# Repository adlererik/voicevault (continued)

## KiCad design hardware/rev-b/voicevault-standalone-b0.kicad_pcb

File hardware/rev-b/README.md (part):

# VoiceVault standalone prototype B0

**Routing in progress — not a working or fabrication-ready PCB.**

[Clean Quilter placement and routing (14 November)](../evidence/2026-11-14/quilter-clean-start/README.md) is now running with the same selected circuit/parts, zero previous tracks/vias/pours, and 292 components for Quilter to place. Its own fanout and routing are enabled; only 22 mechanical/access/antenna anchors remain fixed. All prior work is backed up. The earlier 89%-routed result failed native review; the next corrected trial failed without routed candidates after 29h 27m. Neither replaced the live PCB. [Full history and limits](QUILTER_ROUTING.md).

VoiceVault moves plaintext voice, keys, contacts and call approval into a dedicated device. An already compromised phone carries encrypted records over BLE. This custom rectangular SMD board uses the identified **Trezor Safe 7 TS7 rev_D core ICs**, with added wired headset audio, physical microphone disconnect, offline microSD and separate computer-debug connections. It replaces the earlier development-board carrier as the active hardware design.

The current native KiCad project contains **296 electrical components, 14 board-only probe pads and four mounting holes** on a provisional **70 × 45 mm**, six-layer, 1.0 mm board. Components are placed on both sides. The latest complete-board autorouter checkpoint **fails native DRC: 280 connections remain unrouted, with 33 layout errors and 100 warnings**; exact sourcing and HDI stackup are unresolved, and no physical board has been tested. [Machine-readable status](STATUS.json) · [Recorded evidence and images](../evidence/2026-11-12/README.md)

*Native KiCad exports, front and rear. RF copper and ground pours are present; most signal and power routing remains incomplete.*

## Open and inspect

From the repository root, run `./hardware/open`. The launcher opens one PCB editor and reuses it to limit memory use. Open `voicevault-standalone-b0.kicad_pro` in KiCad to inspect the root schematic and its **18 child sheets**. Keep the large schematic/3D viewers closed when running routing studies on this computer.

KiCad 10.0.8 uses the local `voicevault-kicad` MCP connection through its official IPC API. Circuit simulation uses **ngspice 47 directly**, preserving actual netlists, logs and measurements. MCP is useful for editor interaction; it is not required to run a command-line simulator. [Tool setup](../README.md)

```sh
./hardware/check --design-only --spice
```

This runs native schematic/pad/net checks, ST ball/function comparisons, ERC/DRC, an antenna-rule negative control, **799 ngspice model cases**, and the explicit power-allocation study. Exit 0 with `--design-only` means the available checks passed. The report still says **manufacturing blocked**. Without that option, exit 2 preserves the blocked release verdict. Exit 1 means a check failed. The historical carrier checks remain available as `./hardware/check --rev-a --design-only`.

## Circuit architecture

| Area | Current circuit intent |
|---|---|
| Trusted compute | STM32U5G9ZJJ6Q, UFBGA144, with local clocks, reset, decoupling and internal-SMPS network. The local symbol restores two power balls missing in the installed library. All 144 ball names and 29 selected peripheral functions are compared with separately pinned ST data. |
| Power and battery | nPM1300 dual 200 mA bucks/charger; USB power-only entry, diode-isolated Qi entry, protected battery connector and external cell-temperature input. USB has no D+/D− contacts. Charging configuration and thermal qualification remain open. |
| Secure elements | TROPIC01 and OPTIGA Trust M on MCU-only buses with local power gates. These circuits do not demonstrate lifecycle configuration, entropy quality or secret protection on real silicon. |
| Hostile radio boundary | nRF52832-CIAA with separate SWD and radio power, fixed-direction SN74AXC4T774 bridges, reset control and default-disabled interface. UART carries bounded records; the radio has no audio, secure-element or MCU-debug wires. Electrical fault containment still needs bench tests. |
| Voice | TLV320AIC3204, SAI1 full duplex, dedicated switched audio regulator, CTIA 3.5 mm headset jack, headphone DC-blocking networks, ESD parts and a physical microphone disconnect. All codec controls stay on the trusted MCU side. |
| Trusted interface | Newhaven 240 × 320 display/touch candidate, local reset/update buttons and DRV2624 haptic driver. These require new VoiceVault drivers; this is not the Safe 7 private display assembly. |
| Offline updates | Locally powered microSD SPI interface with default-disabled signal bridge. Signed-image, rollback and interrupted-update policies exist in the software model; they have not been ported and qualified as this board's boot/update firmware. |
| Qi | STWLC38 receiver, coil resonance/rectifier components, thermal sensing and disable path. Its host-control bus is separate from PMIC and secure-element buses. Matching, configuration, charging and temperature behavior are unqualified. |
| NFC | ST25R3916B with dedicated regulator, bridges and matching network; default-off intent. Firmware must require an explicit local enrollment action. An NFC transport is not itself proof of contact identity. |
| Bench access | Main STDC14 and independent Nordic SWD headers, 14 probe pads and removable audio-current link. Prototype debug access deliberately exposes memory/firmware to trusted lab equipment. |

Read [circuit and power review](CIRCUIT_REVIEW.md), [computer connection and bring-up](DEBUG_AND_BRINGUP.md), and [display/battery adaptations](DISPLAY_BATTERY_CANDIDATES.md) before hardware work.

## Exact reference and differences

The source is pinned to trezor/trezor-hardware commit `d99ad42320a19875c124445195fa56f0dbaff6db`. The actual Safe 7 MCU is **STM32U5G9ZJJ6Q in UFBGA144**, not the LQFP144 STM32U5G9ZJT6Q on the DK2 reference board. The earlier DK2 pin allocations and hardware measurements cannot be assumed to apply to this PCB. Actual silicon revision is not yet verified.

The ten core selections are STM32U5G9ZJJ6Q, nPM1300-CAAA, TPS3420DDRYR, STWLC38JRM, nRF52832-CIAA, ST25R3916B-BWLT, SLS32AIA010MKUSON10XTMA2, TPS61062YZFR, DRV2624YFFR and the TROPIC01 family. TPS61062's `R` suffix selects tape/reel packaging. **TROPIC01's orderable silicon/provisioning revision remains unresolved. OPTIGA's reference order code is NRND.** [Core source table](core-parts.csv)

The published Safe 7 release contains PDFs and board views; it does not supply a complete editable manufacturing project or its private display/battery assemblies. This is a new VoiceVault layout, with catalogue display/battery candidates and added audio/card/debug circuitry. AO3401A power-gate FETs are an explicit adaptation from the reference CSD25501F3. New crystals, antenna/coil geometry, power loads and enclosure need their own validation. No Trezor factory identities, attestation keys or certification are reproduced.

## What the evidence establishes

The native export and actual PCB pads agree for 1,026 schematic-connected nodes and 124 intentional NC pins. The schematic's 323 exported net records include those virtual NC records; the PCB has **199 named copper nets**. The saved pre-autoroute check had zero ERC issues and zero layout violations. After the complete-board SES import and copper refill, native KiCad reports **280 open connections, 33 layout errors and 100 warnings**. The detailed list and independent full ratsnest both report 280. [Final native result](../evidence/2026-11-12/autoroute/README.md).

The antenna restriction is tested on a copy: headless KiCad rejects an unrelated track and a ground via inside the reserved area, and permits the RF-feed track. The live design is checked to remain unchanged. This verifies a CAD rule, not antenna performance or isolation from a physical attacker.

The 799 SPICE cases cover 27 passive MCU-supply sensitivities, 36 headphone cases, 32 microphone/contact cases and 704 static backlight load/fault cases. **They use explicit ideal sources and assumed impedances; no MCU, codec, converter control-loop, battery, RF or charging silicon model is supplied.** [Models, measurements and limits](SPICE_RESULTS.md)

The historical live checkpoint uses official, unmodified **FreeRouting 2.5.0**, headlessly on OpenJDK 25.0.4.1. Its 30-minute job deadline produced an SES containing 1,863 track segments and 274 vias (53 laser). The complete copper result was imported through kipy into the live KiCad editor, preserving all 314 component placements and the original zones, then the zones were refilled. **This is an unfinished routing checkpoint:** native DRC found two antenna-area violations, twelve undersized tracks, nineteen starved thermals and one hundred dangling-copper warnings, plus 280 open connections. [Run, files and actual native DRC](../evidence/2026-11-12/autoroute/README.md).

The prior 448-item checkpoint and older timed-out, unapplied studies are retained as historical evidence. [Routing workflow, bridge and process assumptions](ROUTING.md). Power widths, return paths, clock/analog routing, fine-pitch assembly and the factory stackup still need review; no constraints were relaxed to make this result pass.

[Manufacturing-cost research](MANUFACTURING_COST.md) covers four assemblies delivered to Sweden. The routing target is a provisional six-layer first-order HDI construction, with purchasing left open. No supplier is proven cheapest by a complete delivered quotation.

## Manufacturing release is blocked

[circuit-inventory.csv](circuit-inventory.csv) lists every native electrical component and its current requirements. It is **not a JLCPCB assembly BOM**: generic passives, some connector/assembly variants, lifecycle issues and procurement acceptance are still unresolved. The source inventory of 243 upstream component-unit records is historical reference data, not this board's BOM.

The [13 November parts shortlist](PARTS_SELECTION.md) adds catalogue candidates for 182 components in 29 order-code groups, with primary sources, nominal-rating checks and quantities for four fitted boards. Another 56 components still lack a candidate. Tolerance mismatches are explicitly rejected/held. The separate C502 battery-decoupling correction passed native checks on an isolated copy; it is not in the live board, but is included in the clean cloud input. Neither the shortlist nor the correction is an assembly release.

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
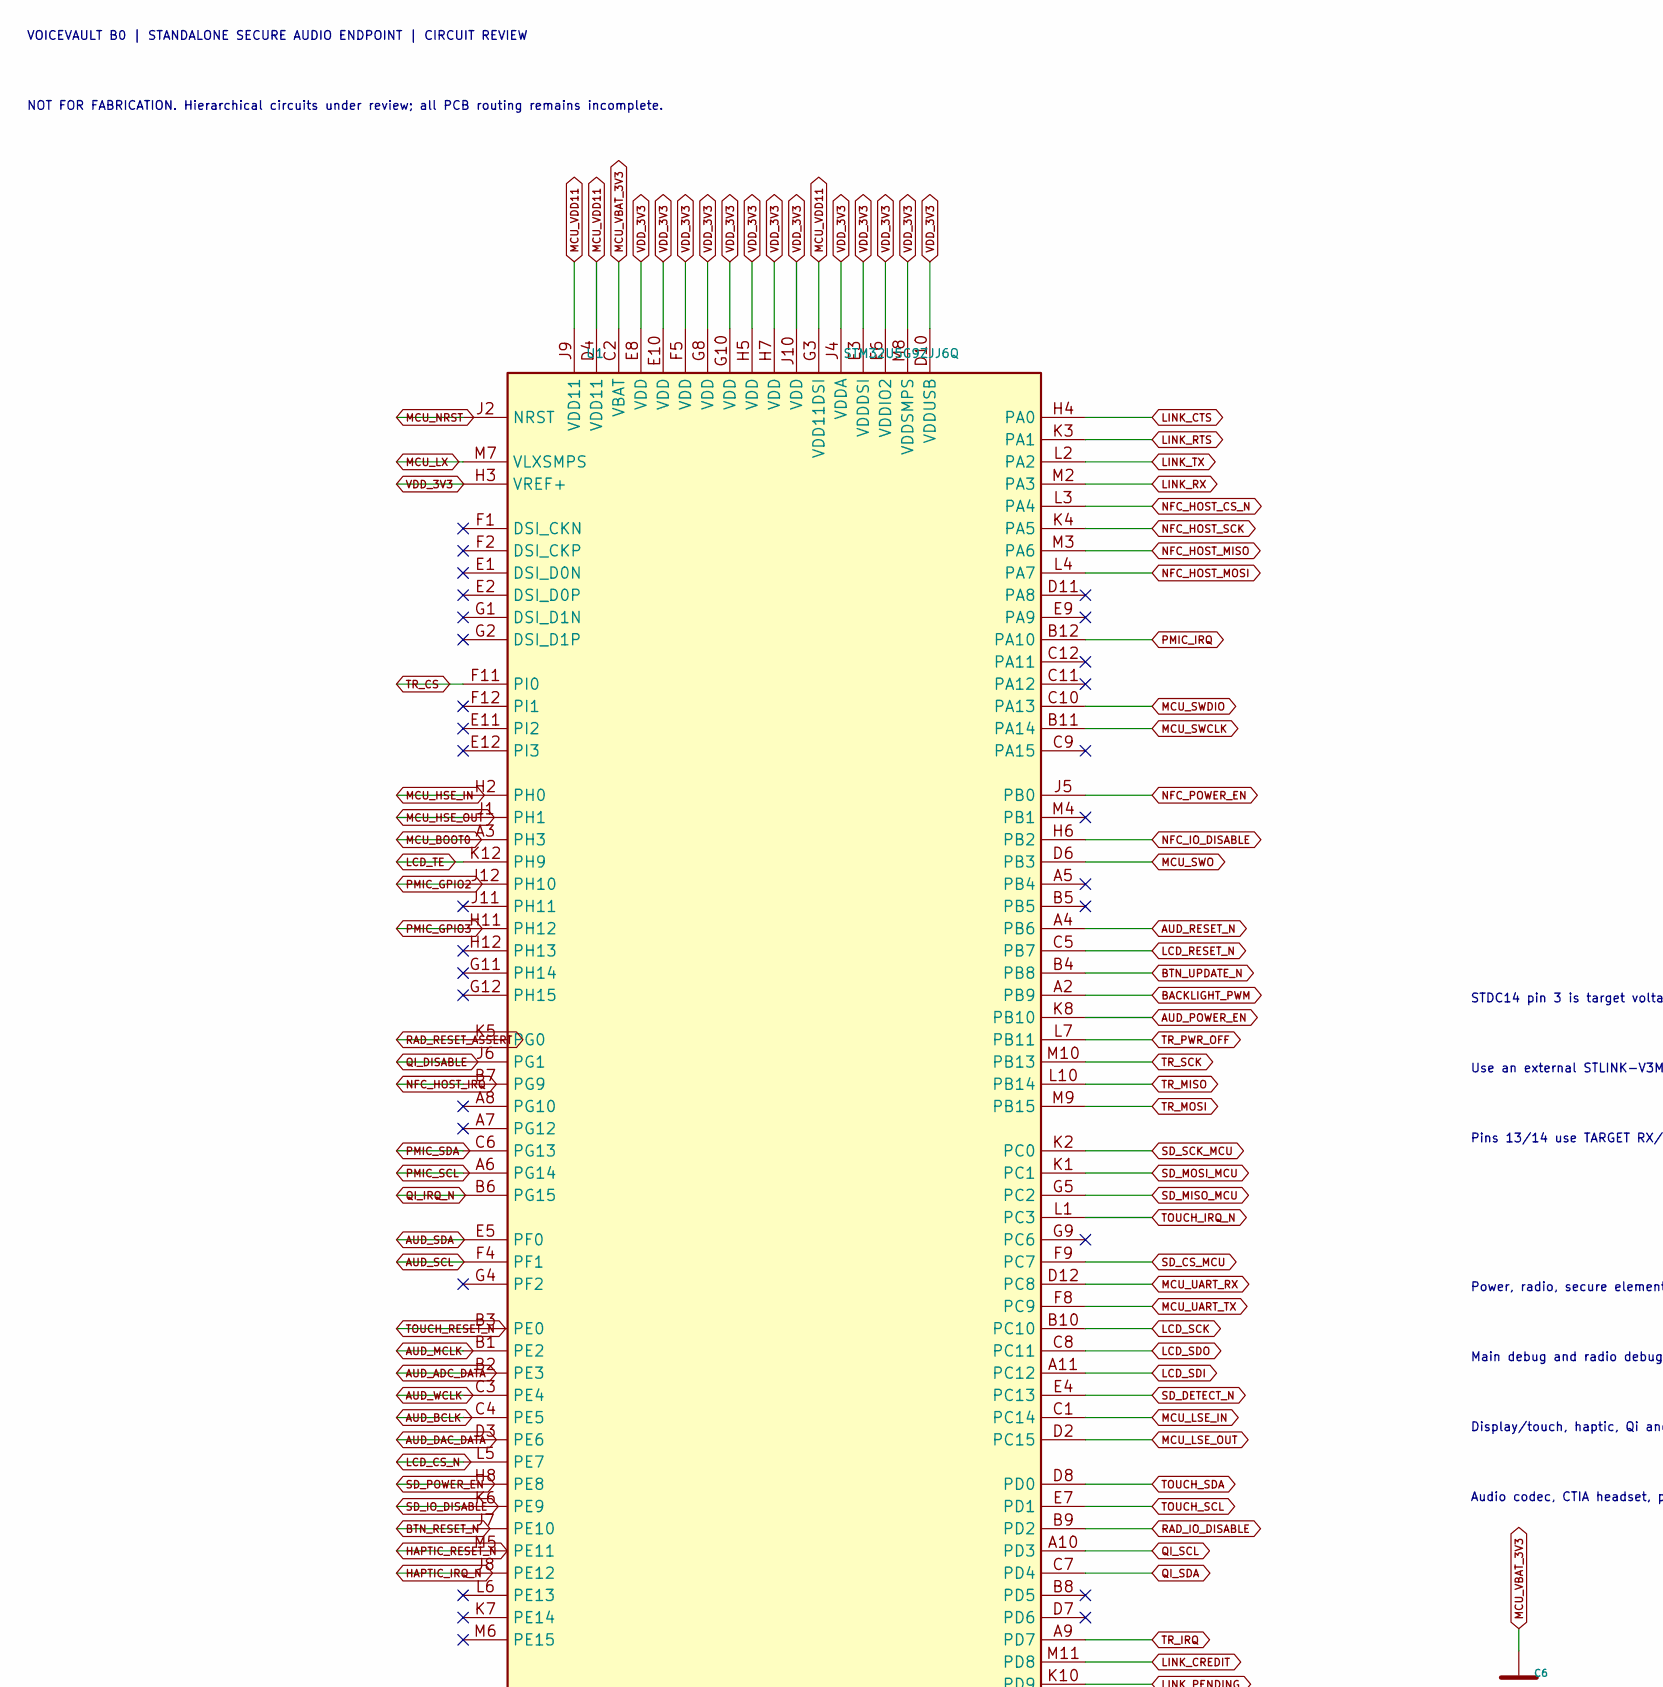
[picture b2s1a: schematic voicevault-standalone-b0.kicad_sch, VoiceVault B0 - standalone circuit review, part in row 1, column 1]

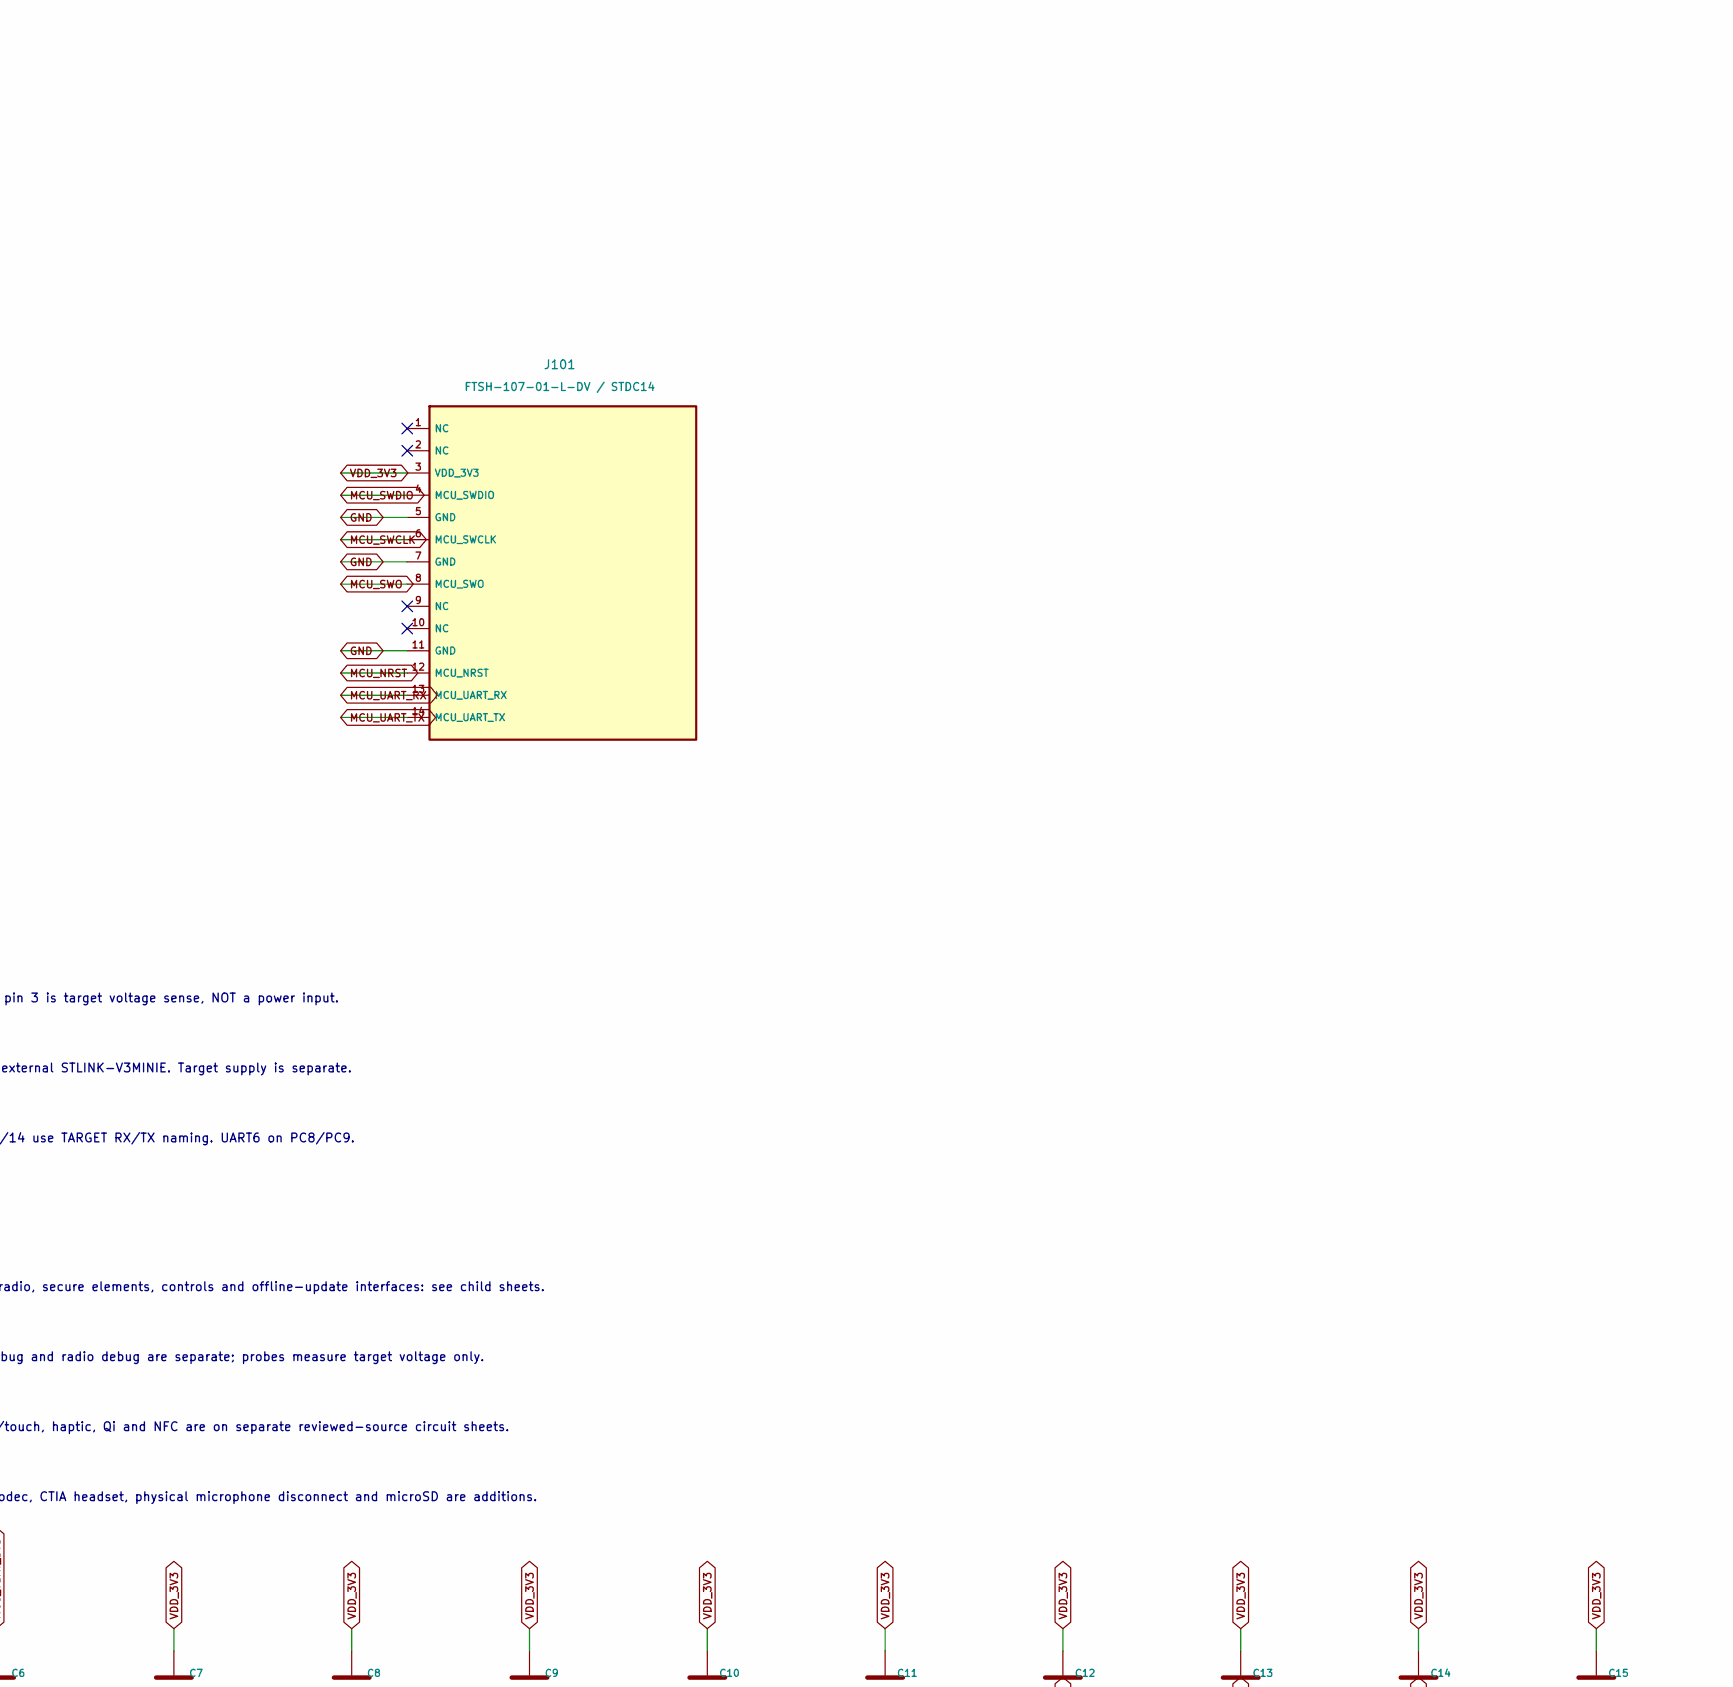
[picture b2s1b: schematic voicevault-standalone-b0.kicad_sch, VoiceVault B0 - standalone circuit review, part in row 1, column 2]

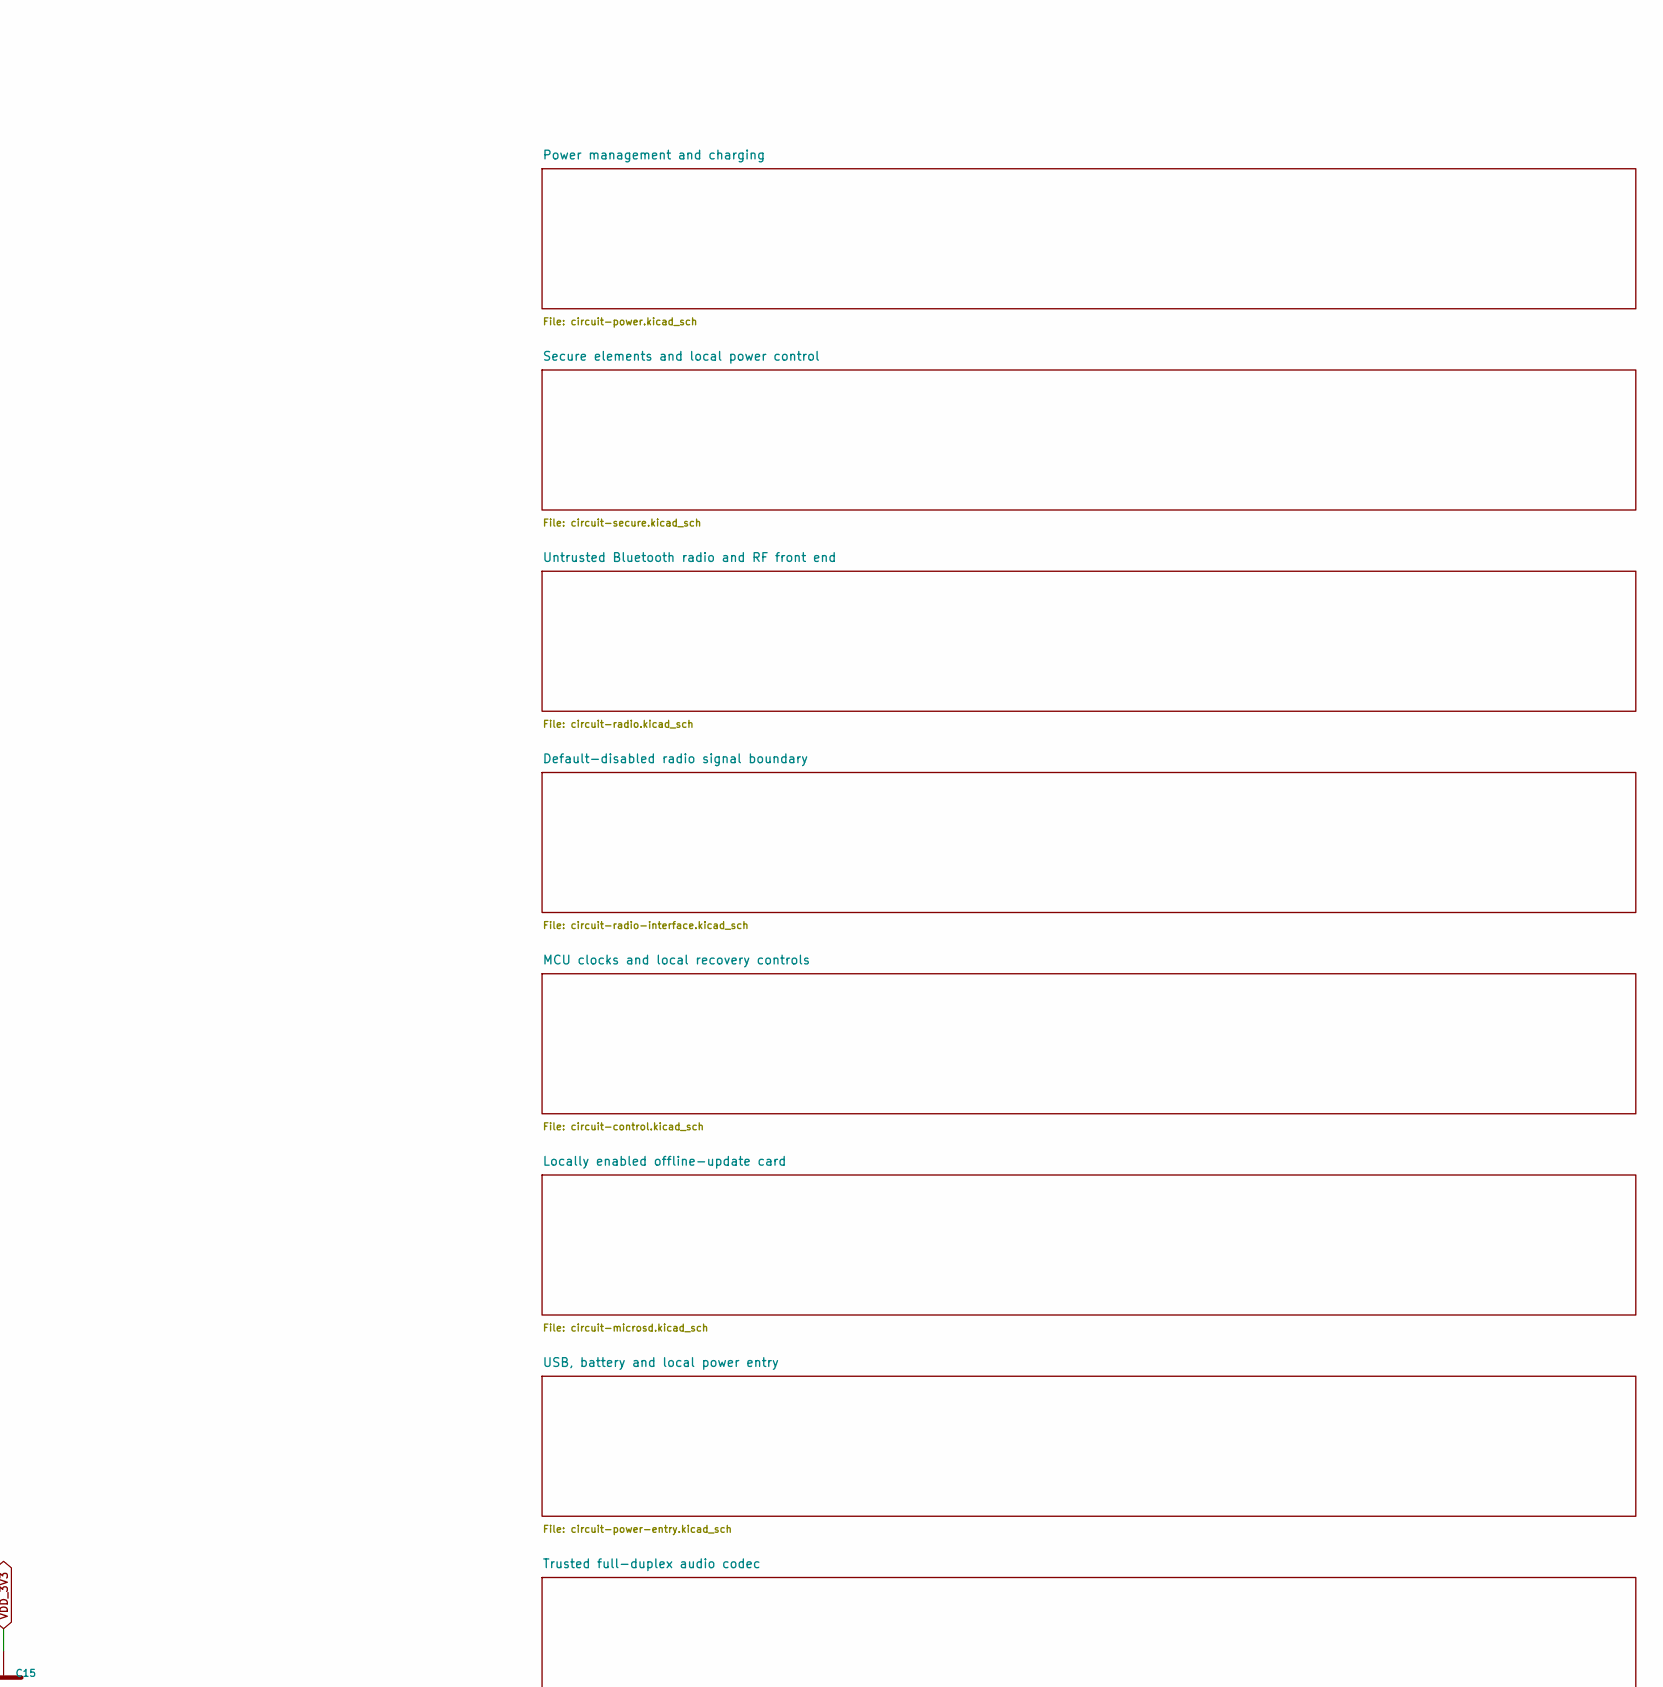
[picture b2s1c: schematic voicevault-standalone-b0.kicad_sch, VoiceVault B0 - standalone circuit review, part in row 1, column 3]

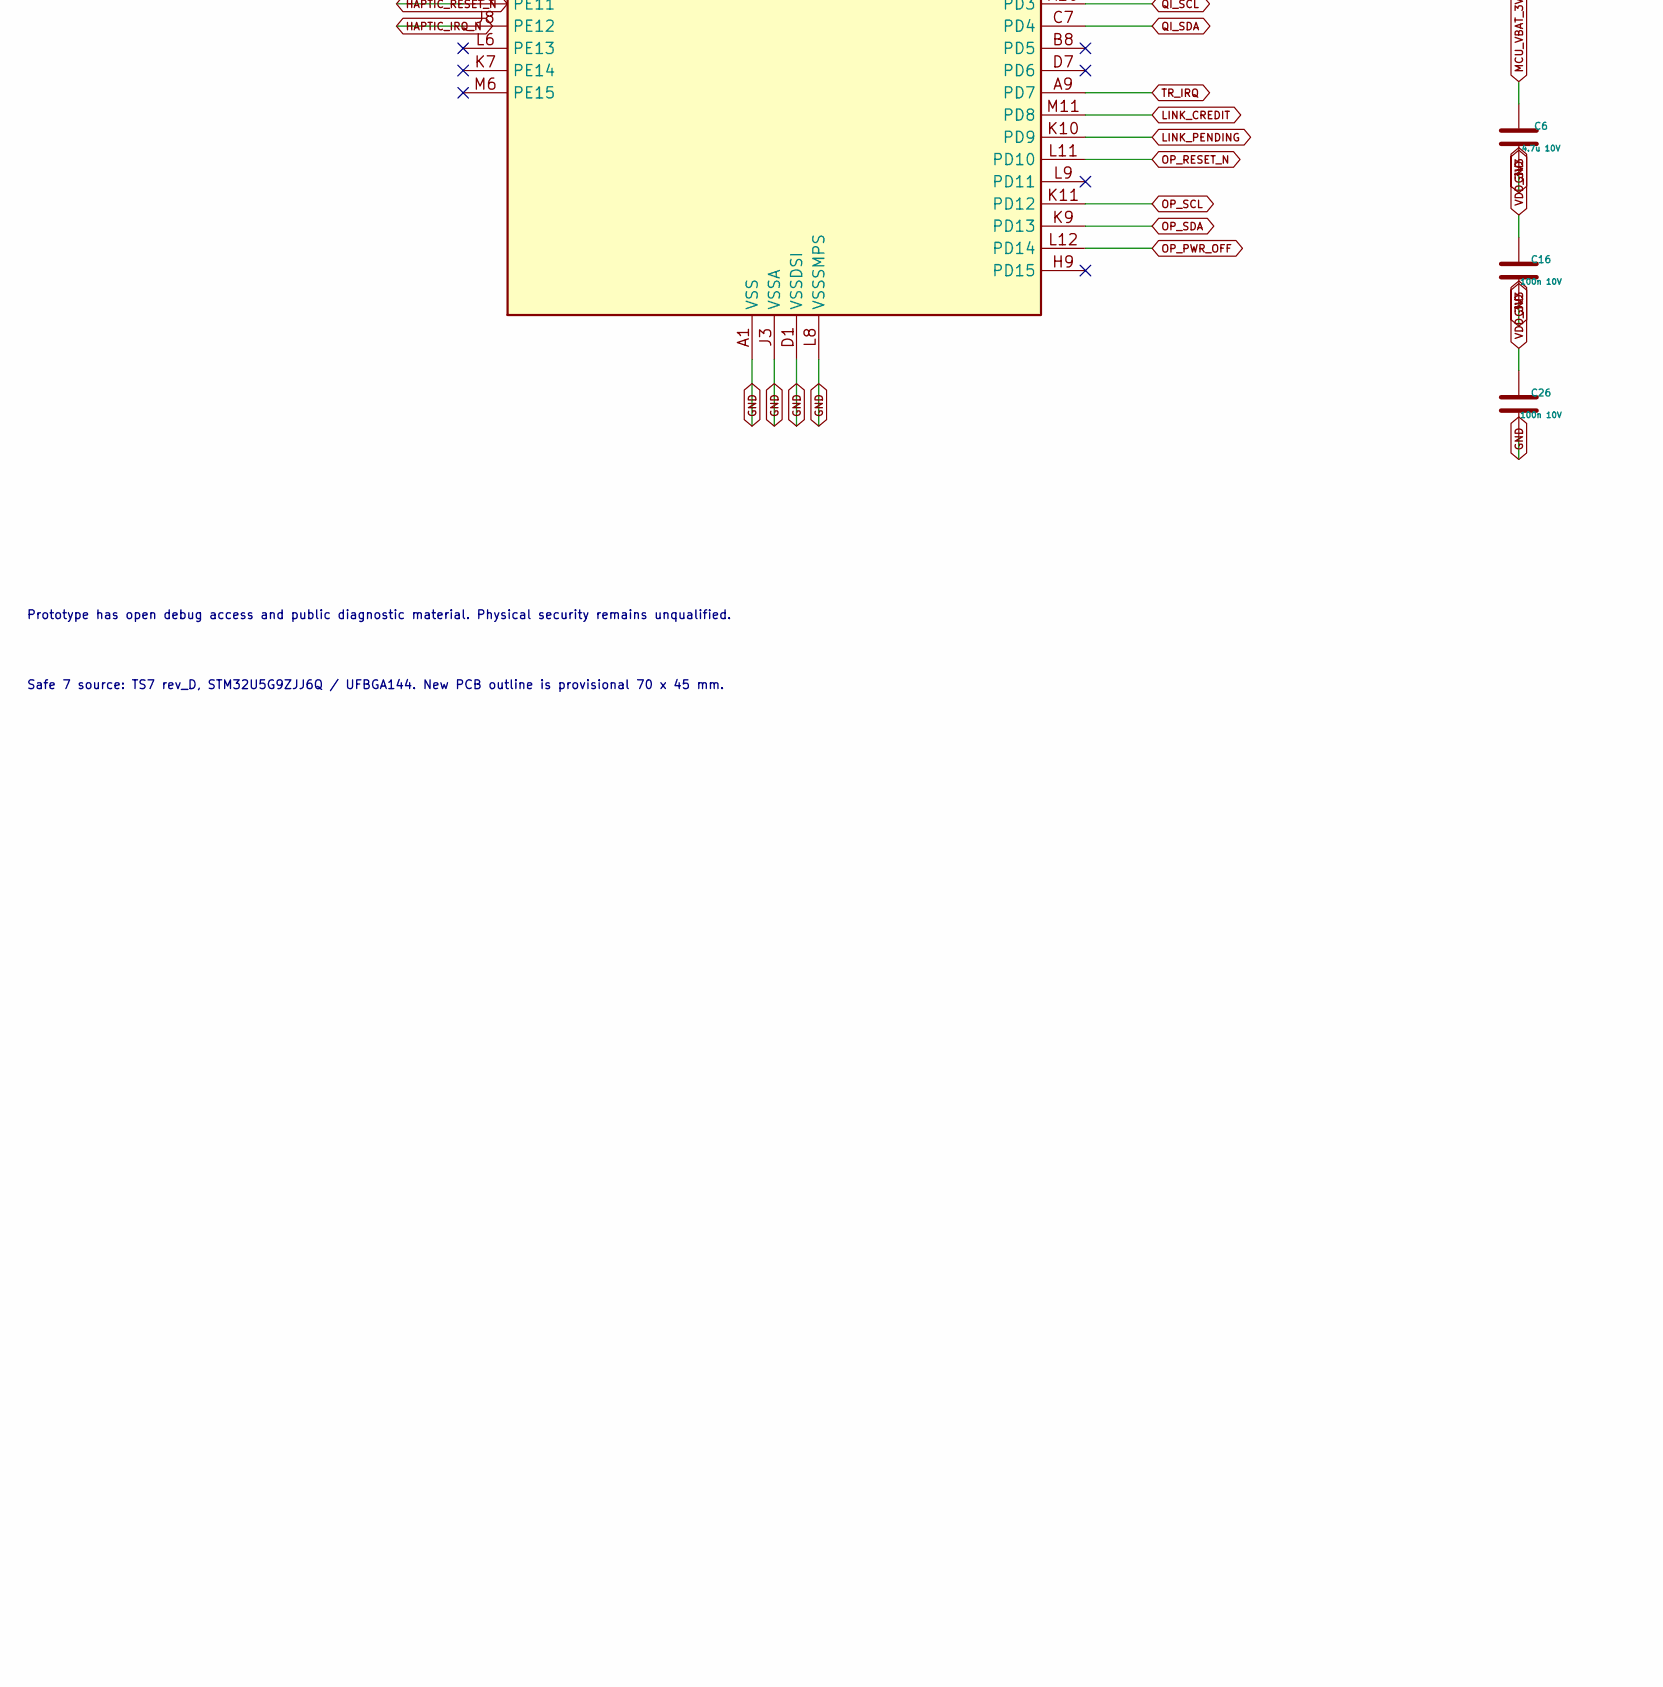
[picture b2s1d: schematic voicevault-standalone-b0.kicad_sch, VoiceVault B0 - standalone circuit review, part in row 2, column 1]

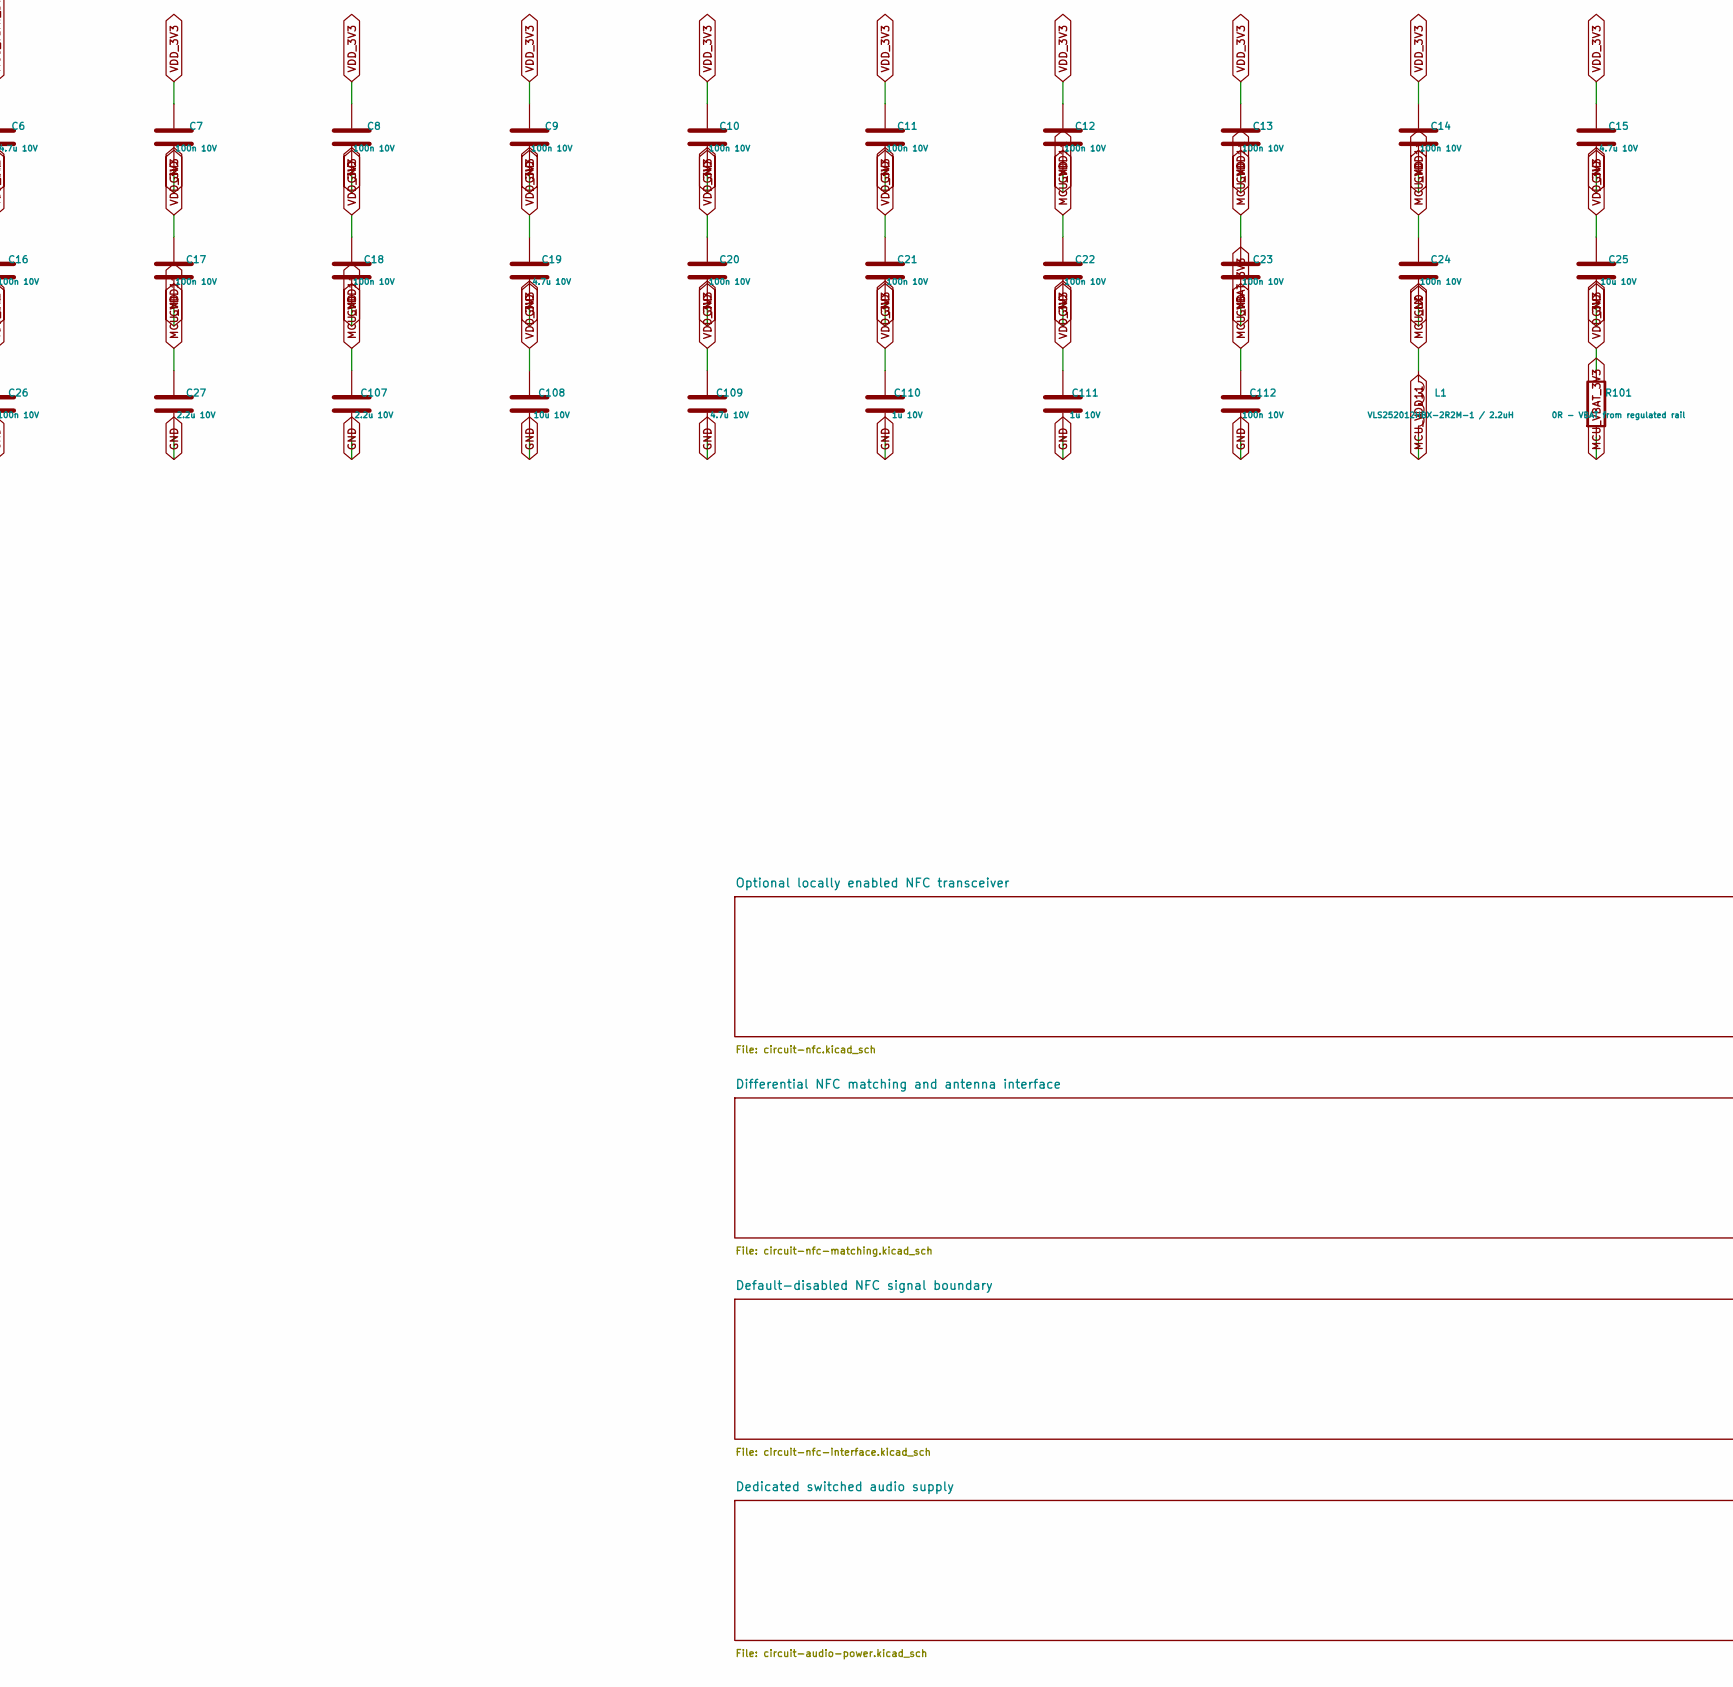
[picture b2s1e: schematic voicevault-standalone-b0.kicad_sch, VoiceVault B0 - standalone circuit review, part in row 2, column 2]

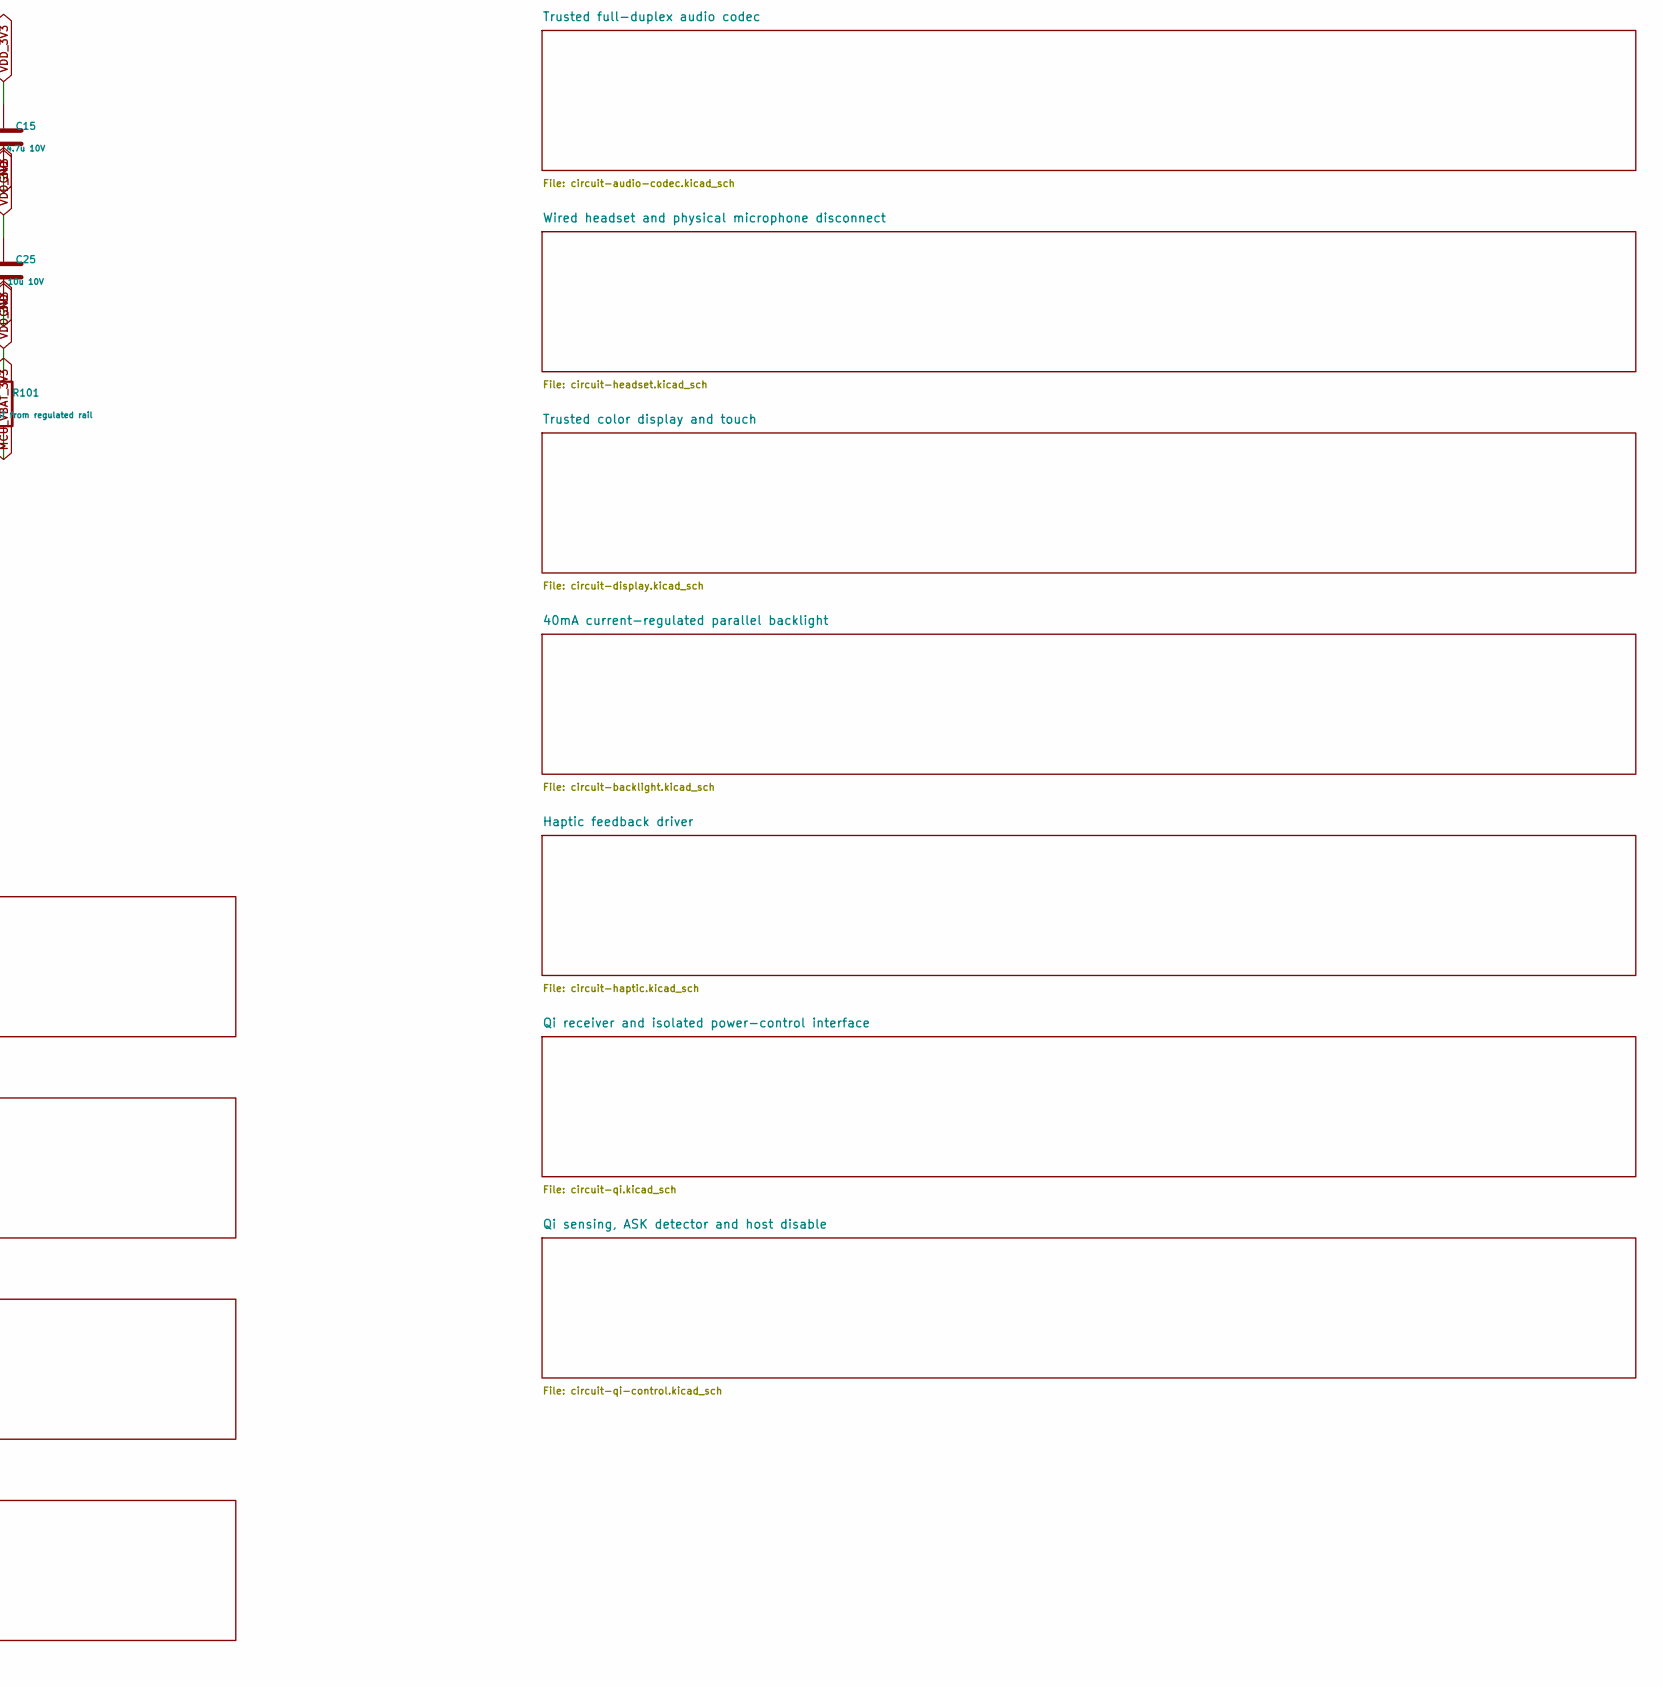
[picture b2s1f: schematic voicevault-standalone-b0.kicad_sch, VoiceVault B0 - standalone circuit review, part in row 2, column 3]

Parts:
C6, C15, C19, C109: 4.7u 10V; C_0603_1608Metric
C7, C8, C9, C10, C11, C12, C13, C14, C16, C17, C18, C20, C21, C22, C23, C24, C26, C112: 100n 10V; C_0402_1005Metric
C25, C108: 10u 10V; C_0805_2012Metric
C27, C107: 2.2u 10V; C_0603_1608Metric
C110, C111: 1u 10V; C_0603_1608Metric
J101: FTSH-107-01-L-DV / STDC14; Samtec_FTSH-107-01-L-DV
L1: VLS252012HBX-2R2M-1 / 2.2uH; L_1008_2520Metric
R101: 0R - VBAT from regulated rail; R_0402_1005Metric
U1: STM32U5G9ZJJ6Q; UFBGA-144_10x10mm_Layout12x12_P0.8mm

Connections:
AUD_ADC_DATA: U1.B2 (PE3); also elsewhere on the board
AUD_BCLK: U1.C4 (PE5); also elsewhere on the board
AUD_DAC_DATA: U1.D3 (PE6); also elsewhere on the board
AUD_MCLK: U1.B1 (PE2); also elsewhere on the board
AUD_POWER_EN: U1.K8 (PB10); also elsewhere on the board
AUD_RESET_N: U1.A4 (PB6); also elsewhere on the board
AUD_SCL: U1.F4 (PF1); also elsewhere on the board
AUD_SDA: U1.E5 (PF0); also elsewhere on the board
AUD_WCLK: U1.C3 (PE4); also elsewhere on the board
BACKLIGHT_PWM: U1.A2 (PB9); also elsewhere on the board
BTN_RESET_N: U1.J7 (PE10); also elsewhere on the board
BTN_UPDATE_N: U1.B4 (PB8); also elsewhere on the board
GND: C6.2, C7.2, C8.2, C9.2, C10.2, C11.2, C12.2, C13.2, C14.2, C15.2, C16.2, C17.2, C18.2, C19.2, C20.2, C21.2, C22.2, C23.2, C24.2, C25.2, C26.2, C27.2, C107.2, C108.2, C109.2, C110.2, C111.2, C112.2, J101.5 (GND), J101.7 (GND), J101.11 (GND), U1.A1 (VSS), U1.A12 (VSS), U1.D1 (VSSDSI), U1.D5 (VSS), U1.D9 (VSS), U1.F3 (VSSDSI), U1.F6 (VSS), U1.F7 (VSS), U1.F10 (VSS), U1.G6 (VSS), U1.G7 (VSS), U1.H1 (VSSDSI), U1.H10 (VSS), U1.J3 (VSSA), U1.L8 (VSSSMPS), U1.M1 (VSS), U1.M12 (VSS); also elsewhere on the board
HAPTIC_IRQ_N: U1.J8 (PE12); also elsewhere on the board
HAPTIC_RESET_N: U1.M5 (PE11); also elsewhere on the board
LCD_CS_N: U1.L5 (PE7); also elsewhere on the board
LCD_RESET_N: U1.C5 (PB7); also elsewhere on the board
LCD_SCK: U1.B10 (PC10); also elsewhere on the board
LCD_SDI: U1.A11 (PC12); also elsewhere on the board
LCD_SDO: U1.C8 (PC11); also elsewhere on the board
LCD_TE: U1.K12 (PH9); also elsewhere on the board
LINK_CREDIT: U1.M11 (PD8); also elsewhere on the board
LINK_CTS: U1.H4 (PA0); also elsewhere on the board
LINK_PENDING: U1.K10 (PD9); also elsewhere on the board
LINK_RTS: U1.K3 (PA1); also elsewhere on the board
LINK_RX: U1.M2 (PA3); also elsewhere on the board
LINK_TX: U1.L2 (PA2); also elsewhere on the board
MCU_BOOT0: U1.A3 (PH3); also elsewhere on the board
MCU_HSE_IN: U1.H2 (PH0); also elsewhere on the board
MCU_HSE_OUT: U1.J1 (PH1); also elsewhere on the board
MCU_LSE_IN: U1.C1 (PC14); also elsewhere on the board
MCU_LSE_OUT: U1.D2 (PC15); also elsewhere on the board
MCU_LX: L1.1, U1.M7 (VLXSMPS)
MCU_NRST: J101.12 (MCU_NRST), U1.J2 (NRST); also elsewhere on the board
MCU_SWCLK: J101.6 (MCU_SWCLK), U1.B11 (PA14)
MCU_SWDIO: J101.4 (MCU_SWDIO), U1.C10 (PA13)
MCU_SWO: J101.8 (MCU_SWO), U1.D6 (PB3)
MCU_UART_RX: J101.13 (MCU_UART_RX), U1.D12 (PC8)
MCU_UART_TX: J101.14 (MCU_UART_TX), U1.F8 (PC9)
MCU_VBAT_3V3: C6.1, C112.1, R101.2, U1.C2 (VBAT)
MCU_VDD11: C22.1, C23.1, C24.1, C27.1, C107.1, L1.2, U1.D4 (VDD11), U1.G3 (VDD11DSI), U1.J9 (VDD11); also elsewhere on the board
NFC_HOST_CS_N: U1.L3 (PA4); also elsewhere on the board
NFC_HOST_IRQ: U1.B7 (PG9); also elsewhere on the board
NFC_HOST_MISO: U1.M3 (PA6); also elsewhere on the board
NFC_HOST_MOSI: U1.L4 (PA7); also elsewhere on the board
NFC_HOST_SCK: U1.K4 (PA5); also elsewhere on the board
NFC_IO_DISABLE: U1.H6 (PB2); also elsewhere on the board
NFC_POWER_EN: U1.J5 (PB0); also elsewhere on the board
OP_PWR_OFF: U1.L12 (PD14); also elsewhere on the board
OP_RESET_N: U1.L11 (PD10); also elsewhere on the board
OP_SCL: U1.K11 (PD12); also elsewhere on the board
OP_SDA: U1.K9 (PD13); also elsewhere on the board
PMIC_GPIO2: U1.J12 (PH10); also elsewhere on the board
PMIC_GPIO3: U1.H11 (PH12); also elsewhere on the board
PMIC_IRQ: U1.B12 (PA10); also elsewhere on the board
PMIC_SCL: U1.A6 (PG14); also elsewhere on the board
PMIC_SDA: U1.C6 (PG13); also elsewhere on the board
QI_DISABLE: U1.J6 (PG1); also elsewhere on the board
QI_IRQ_N: U1.B6 (PG15); also elsewhere on the board
QI_SCL: U1.A10 (PD3); also elsewhere on the board
QI_SDA: U1.C7 (PD4); also elsewhere on the board
RAD_IO_DISABLE: U1.B9 (PD2); also elsewhere on the board
RAD_RESET_ASSERT: U1.K5 (PG0); also elsewhere on the board
SD_CS_MCU: U1.F9 (PC7); also elsewhere on the board
SD_DETECT_N: U1.E4 (PC13); also elsewhere on the board
SD_IO_DISABLE: U1.K6 (PE9); also elsewhere on the board
SD_MISO_MCU: U1.G5 (PC2); also elsewhere on the board
SD_MOSI_MCU: U1.K1 (PC1); also elsewhere on the board
SD_POWER_EN: U1.H8 (PE8); also elsewhere on the board
SD_SCK_MCU: U1.K2 (PC0); also elsewhere on the board
TOUCH_IRQ_N: U1.L1 (PC3); also elsewhere on the board
TOUCH_RESET_N: U1.B3 (PE0); also elsewhere on the board
TOUCH_SCL: U1.E7 (PD1); also elsewhere on the board
TOUCH_SDA: U1.D8 (PD0); also elsewhere on the board
TR_CS: U1.F11 (PI0); also elsewhere on the board
TR_IRQ: U1.A9 (PD7); also elsewhere on the board
TR_MISO: U1.L10 (PB14); also elsewhere on the board
TR_MOSI: U1.M9 (PB15); also elsewhere on the board
TR_PWR_OFF: U1.L7 (PB11); also elsewhere on the board
TR_SCK: U1.M10 (PB13); also elsewhere on the board
VDD_3V3: C7.1, C8.1, C9.1, C10.1, C11.1, C12.1, C13.1, C14.1, C15.1, C16.1, C17.1, C18.1, C19.1, C20.1, C21.1, C25.1, C26.1, C108.1, C109.1, C110.1, C111.1, J101.3 (VDD_3V3), R101.1, U1.D10 (VDDUSB), U1.E3 (VDDDSI), U1.E6 (VDDIO2), U1.E8 (VDD), U1.E10 (VDD), U1.F5 (VDD), U1.G8 (VDD), U1.G10 (VDD), U1.H3 (VREF+), U1.H5 (VDD), U1.H7 (VDD), U1.J4 (VDDA), U1.J10 (VDD), U1.M8 (VDDSMPS); also elsewhere on the board

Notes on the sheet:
VOICEVAULT B0 | STANDALONE SECURE AUDIO ENDPOINT | CIRCUIT REVIEW
NOT FOR FABRICATION. Hierarchical circuits under review; all PCB routing remains incomplete.
STDC14 pin 3 is target voltage sense, NOT a power input.
Use an external STLINK-V3MINIE. Target supply is separate.
Pins 13/14 use TARGET RX/TX naming. UART6 on PC8/PC9.
Power, radio, secure elements, controls and offline-update interfaces: see child sheets.
Main debug and radio debug are separate; probes measure target voltage only.
Display/touch, haptic, Qi and NFC are on separate reviewed-source circuit sheets.
Audio codec, CTIA headset, physical microphone disconnect and microSD are additions.
Prototype has open debug access and public diagnostic material. Physical security remains unqualified.
Safe 7 source: TS7 rev_D, STM32U5G9ZJJ6Q / UFBGA144. New PCB outline is provisional 70 x 45 mm.
